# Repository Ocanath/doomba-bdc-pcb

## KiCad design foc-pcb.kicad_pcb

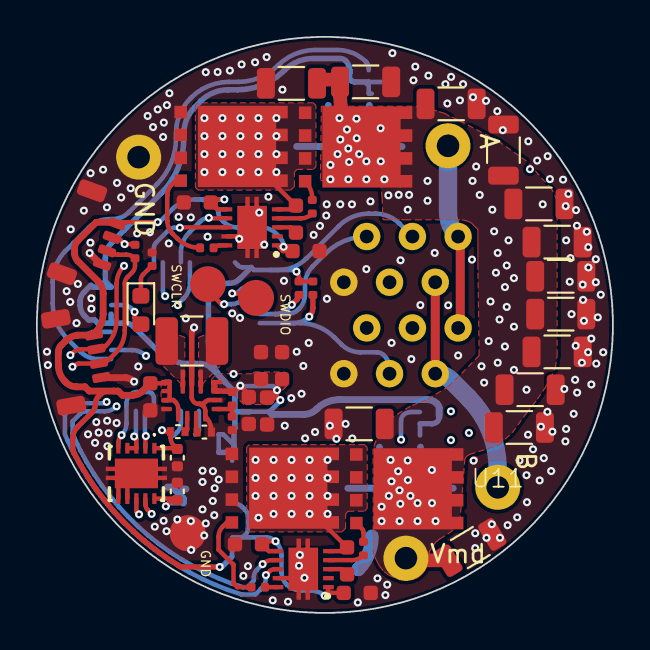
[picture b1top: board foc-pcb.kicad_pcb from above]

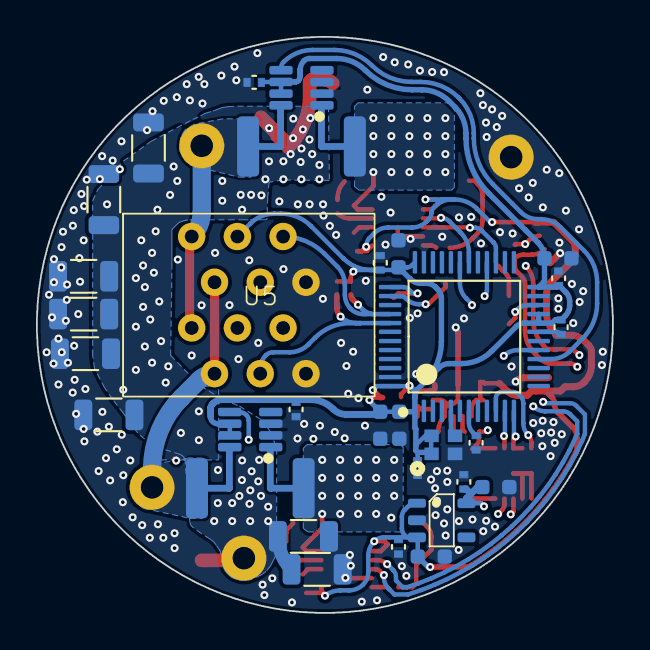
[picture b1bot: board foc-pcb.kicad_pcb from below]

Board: 4 copper layers, 32.0 x 32.0 mm, 88 parts (31 on the bottom side), 43 nets.

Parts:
C1, C4, C5, C12, C13, C15, C16, C20: 4.7uF; C_0603_1608Metric
C3, C6, C8, C10, C19, C21, C32, C34, C51, C52, C55, C56: 100nF; C_0402_1005Metric
C7, C9, C11, C18, C22, C23, C24, C25, C33: 10uF; C_0603_1608Metric
C26, C27, C28, C29, C30, C31, C37, C38, C39, C40, C41, C42, C43, C44, C45, C47, C49, C50, C54, C59, C61: 10uF; C_1206_3216Metric
D1: LED Green 0603; LED_0603_1608Metric
IC1: THVD2450VDRCR; THVD2410VDRCR
L1: 1277AS-H-1R0M=P2; L_1210_3225Metric
Q1, Q2, Q7, Q8: CSD18540Q5B; 8-PowerTDFN
R1, R2, R11, R12: 10; R_0402_1005Metric
R3, R13: PA2512FKF7T0R003E; R_2512_6332Metric
R4: 470; R_0402_1005Metric
R5, R6: 10k; R_0402_1005Metric
R9: 120; R_0402_1005Metric
R10: 100k; C_0402_1005Metric
R14: 470k; R_0402_1005Metric
R15: 150k; R_0402_1005Metric
U1, U8: UCC272847; DFN-10-GATEDRIVER
U2: STM32G431CBT6; LQFP48-STM32
U3, U9: INA241B4IDDFR; SOT-23-8
U5: RBB06DHHN
U6: SPX3819M5-L-5-0; SOT-23-5
U10: TPS63070; VQFN-TPS63070
U11, U15, U19, U20: PowerHole
U12: C2901617; ECS-1633-480-BN-TR
U17, U18: DF52-4S-0.8H(21)
U23, U24, U25: SMD_PROG_PAD

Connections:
+3V3: C6.1, C7.1, C8.1, C9.1, C10.1, C11.1, C18.1, C19.1, C22.1, C23.1, C24.1, C25.1, C51.2, C55.1, C56.1, IC1.1 (VIO), R5.1, R6.1, R10.1, R14.1, U2.1 (VBAT), U2.20 (VREF+), U2.21 (VDDA), U2.24 (VDD), U2.36 (VDD), U2.48 (VDD), U3.6 (Vs), U3.7 (REF1), U5.3A, U9.6 (Vs), U9.7 (REF1), U10.7,8 (VOUT), U12.1 (Enable/Disable), U12.4 (VDD)
/+5V0: C33.1, C34.1, C52.2, IC1.10 (VCC), U6.5 (VOUT)
/HALL_ENCODER: R5.2, U2.41 (PB4), U5.4B
/PHASE_A: R13.2, U5.1A, U5.1B, U9.8 (IN+), U20.1
/PHASE_B: R3.2, U3.8 (IN+), U5.2A, U5.2B, U11.1
/PSU_TPS63070RNMR/FB: R14.2, R15.1, U10.5 (FB)
/PhaseA/HS: C4.2, Q7.1 (S), Q8.3 (D), R13.1, U8.5 (HS), U9.1 (IN-)
/PhaseB/HS: C1.2, Q1.1 (S), Q2.3 (D), R3.1, U1.5 (HS), U3.1 (IN-)
/RS485/RS1_A: IC1.8 (A), R9.1, U17.2, U18.2
/RS485/RS1_B: IC1.9 (B), R9.2, U17.3, U18.3
/RS485/UART_DE: IC1.3 (DE), IC1.4 (~RE), U2.12 (PA4)
/RS485/UART_RX: IC1.2 (R), U2.11 (PA3)
/RS485/UART_TX: IC1.5 (D), U2.10 (PA2)
/STM32/ISENSE_A: U2.16 (PB0), U9.5 (OUT)
/STM32/ISENSE_B: U2.17 (PB1), U3.5 (OUT)
/STM32/LED: D1.2 (A), U2.22 (PB10)
/STM32/SWCLK: U2.38 (PA14), U24.1
/STM32/SWDIO: U2.37 (PA13), U23.1
/STM32/TIM1_CH1: U2.30 (PA8), U8.7 (HI)
/STM32/TIM1_CH1N: U2.27 (PB13), U8.8 (LI)
/STM32/TIM1_CH2: U1.7 (HI), U2.31 (PA9)
/STM32/TIM1_CH2N: U1.8 (LI), U2.28 (PB14)
/V_GATEDRIVE: C5.1, C12.1, C13.1, C15.1, C16.1, C20.1, C32.1, U1.1 (VDD), U1.6 (EN), U6.1 (VIN), U6.3 (EN), U8.1 (VDD), U8.6 (EN), U10.1 (PS/SYNC), U10.12,13 (VIN), U10.14 (EN), U17.1, U18.1
/WD: R6.2, U2.40 (PB3), U5.5A
GND: C3.2, C5.2, C6.2, C7.2, C8.2, C9.2, C10.2, C11.2, C12.2, C13.2, C15.2, C16.2, C18.2, C19.2, C20.2, C21.2, C22.2, C23.2, C24.2, C25.2, C26.2, C27.2, C28.2, C29.2, C30.2, C31.2, C32.2, C33.2, C34.2, C37.2, C38.2, C39.2, C40.2, C41.2, C42.2, C43.2, C44.2, C45.2, C47.2, C49.2, C50.2, C51.1, C52.1, C54.2, C55.2, C56.2, C59.2, C61.2, IC1.6 (GND), IC1.7 (SLR), IC1.11 (EP_1), IC1.12 (EP_2), IC1.13 (EP_3), IC1.14 (EP_4), IC1.15 (EP_5), Q2.1 (S), Q8.1 (S), R4.2, R15.2, U1.9 (VSS), U1.11 (PAD), U2.19 (VSSA), U2.23 (VSS), U2.35 (VSS), U2.47 (VSS), U3.2 (GND), U3.3 (REF2), U5.6A, U5.6B, U6.2 (GND), U8.9 (VSS), U8.11 (PAD), U9.2 (GND), U9.3 (REF2), U10.4 (GND), U10.6 (FB2), U10.10 (PGND), U10.15 (VSEL), U12.2 (GND/Case), U17.4, U17.5 (MNT), U17.6 (MNT), U18.4, U18.5 (MNT), U18.6 (MNT), U19.1, U25.1
unnamed: D1.1 (K), R4.1
unnamed: Q1.2 (G), R1.2
unnamed: Q2.2 (G), R2.2
unnamed: Q7.2 (G), R11.2
unnamed: Q8.2 (G), R12.2
unnamed: C1.1, U1.3 (HB)
unnamed: R1.1, U1.4 (HO)
unnamed: R2.1, U1.10 (LO)
unnamed: C3.1, U2.7 (PG10-NRST)
unnamed: C4.1, U8.3 (HB)
unnamed: R11.1, U8.4 (HO)
unnamed: R12.1, U8.10 (LO)
unnamed: L1.1, U10.11 (L1)
unnamed: L1.2, U10.9 (L2)
unnamed: R10.2, U10.2 (PG)
unnamed: C21.1, U10.3 (VAUX)
unnamed: U2.5 (PF0-OSC_IN), U12.3 (OUTPUT)
Vdrive: C26.1, C27.1, C28.1, C29.1, C30.1, C31.1, C37.1, C38.1, C39.1, C40.1, C41.1, C42.1, C43.1, C44.1, C45.1, C47.1, C49.1, C50.1, C54.1, C59.1, C61.1, Q1.3 (D), Q7.3 (D), U15.1

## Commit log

2026-05-18 init commit, vendored brushed dc motor pcb
2026-05-18 switch to 5V excitation for halls which is confirmed working on hardware
2026-05-25 remove gerber
2026-05-25 origin
2026-05-25 tweak pad location
2026-06-04 board clearance
